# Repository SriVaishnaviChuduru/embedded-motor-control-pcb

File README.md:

# Embedded Motor Control PCB

## 📌 Project Overview
This project presents a custom-designed PCB integrating an Arduino Uno and dual L298N motor drivers into a single compact board. The objective was to reduce system size, improve wiring efficiency, and enhance reliability.

## 🚀 Key Features
- Unified PCB integrating Arduino Uno + Dual L298N drivers
- 60% reduction in overall system footprint
- Optimized routing for power and motor driver traces
- Compact and modular embedded system design

## 🛠 Tools Used
- KiCad (Schematic & PCB Layout)
- Fusion 360
- Embedded hardware testing

## 📷 Project Preview

### 🔹 Schematic

### 🔹 PCB Layout

### 🔹 3D View

## 📂 Repository Contents
- KiCad schematic files
- PCB layout files
- Project PDFs
- 3D render images

## 🎯 Learning Outcomes
- PCB schematic capture
- Layout optimization
- Power routing techniques
- Hardware debugging and board bring-up

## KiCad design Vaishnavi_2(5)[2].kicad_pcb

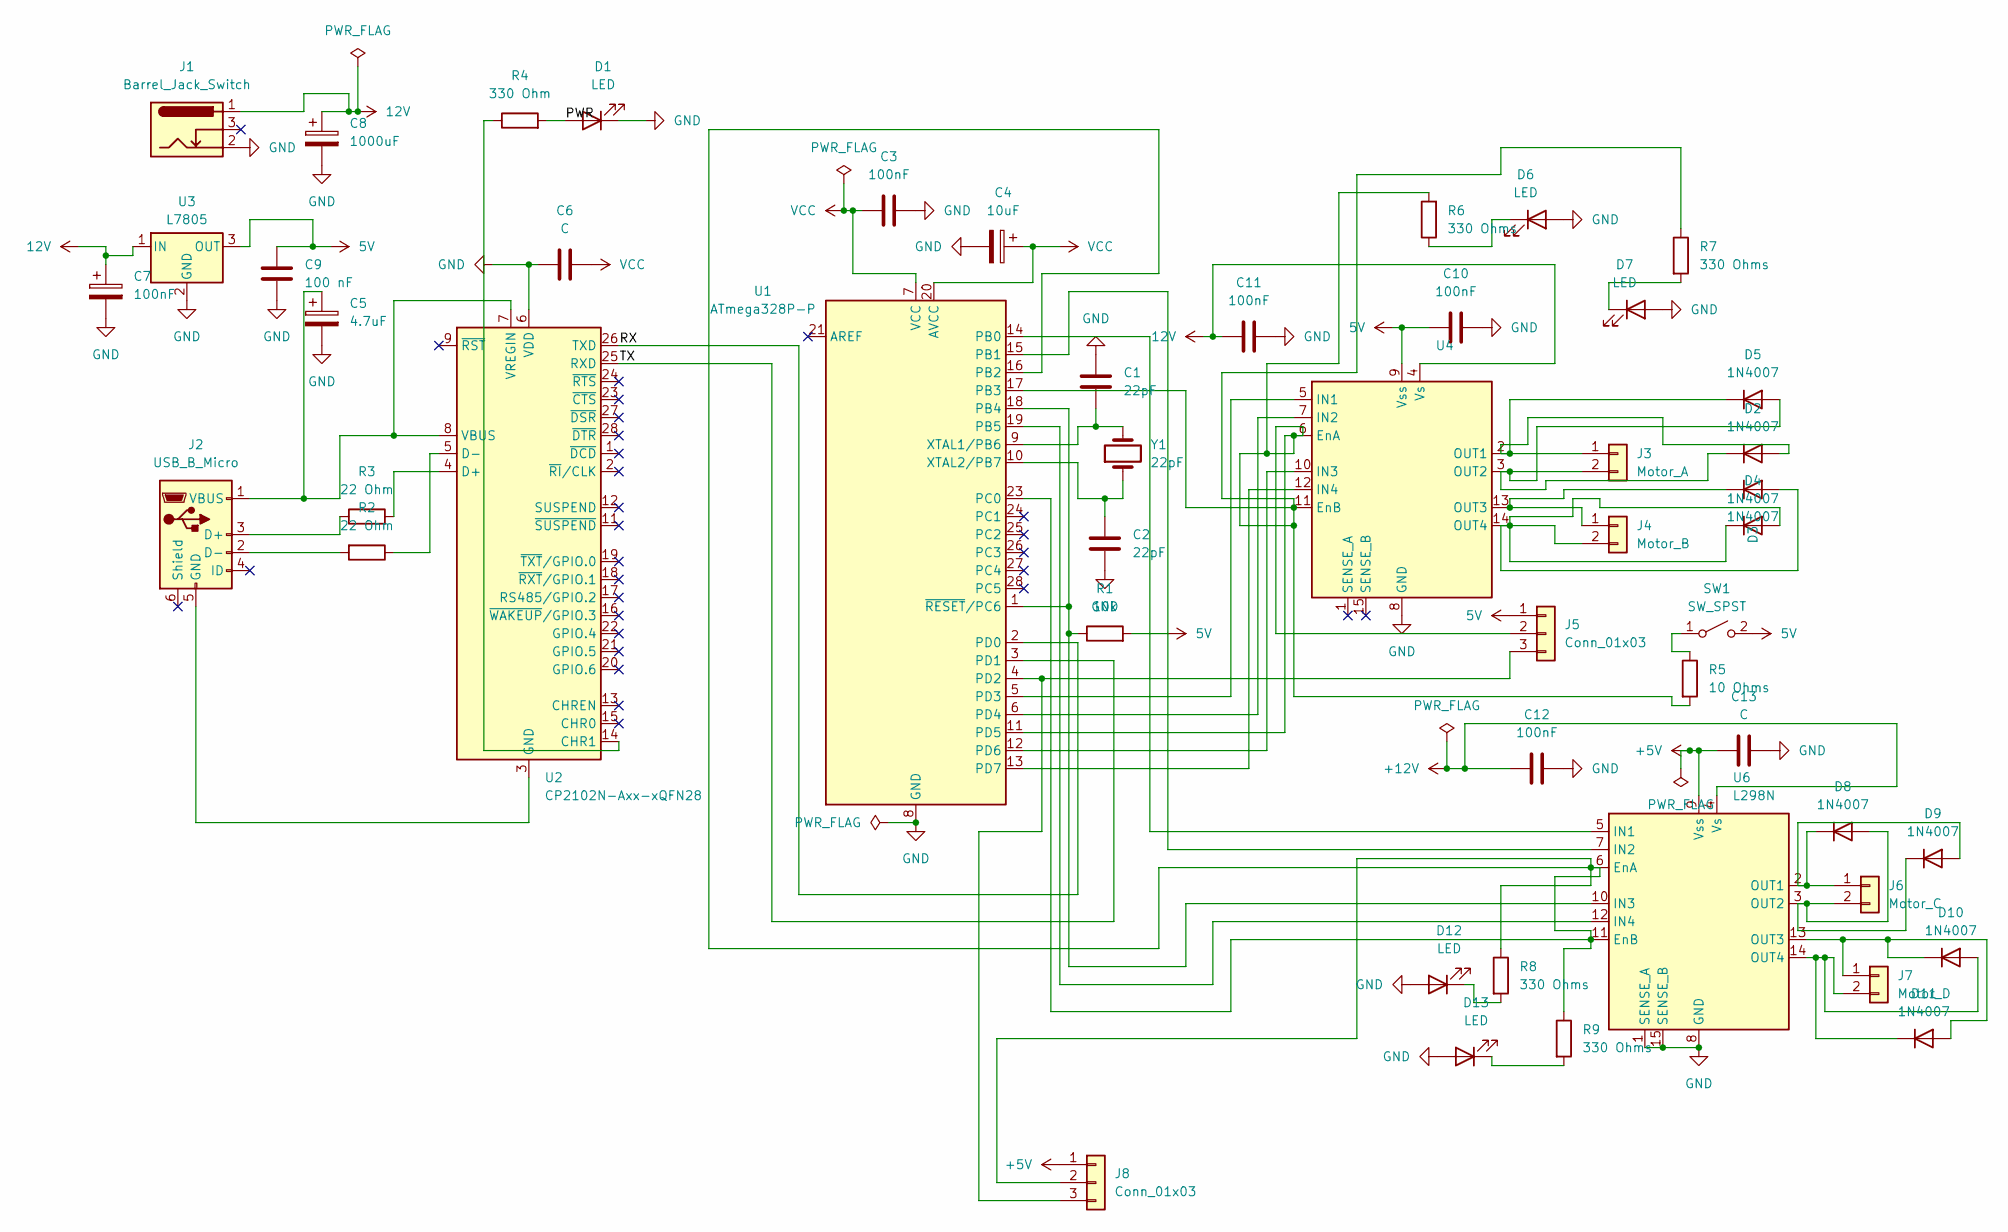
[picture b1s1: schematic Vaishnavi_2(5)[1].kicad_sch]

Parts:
C1, C2: 22pF; C_0805_2012Metric
C3, C7, C10, C11, C12: 100nF; C_0805_2012Metric
C4: 10uF; C_1210_3225Metric
C5: 4.7uF; C_1206_3216Metric
C6, C13: C; C_0805_2012Metric
C8: 1000uF; C_0805_2012Metric
C9: 100 nF; C_0805_2012Metric
D1: LED; TerminalBlock_Xinya_XY308-2.54-2P_1x02_P2.54mm_Horizontal
D2, D3, D4, D5, D8, D9, D10, D11: 1N4007; D_DO-41_SOD81_P10.16mm_Horizontal
D6, D7: LED; LED_BL-FL7680RGB
D12, D13: LED; LED_0805_2012Metric
J1: Barrel_Jack_Switch; BarrelJack_CLIFF_FC681465S_SMT_Horizontal
J2: USB_B_Micro; USB_B_OST_USB-B1HSxx_Horizontal
J3: Motor_A; TerminalBlock_Xinya_XY308-2.54-2P_1x02_P2.54mm_Horizontal
J4: Motor_B; TerminalBlock_Xinya_XY308-2.54-2P_1x02_P2.54mm_Horizontal
J5, J8: Conn_01x03; PinHeader_1x03_P1.00mm_Horizontal
J6: Motor_C; TerminalBlock_Xinya_XY308-2.54-2P_1x02_P2.54mm_Horizontal
J7: Motor_D; TerminalBlock_Xinya_XY308-2.54-2P_1x02_P2.54mm_Horizontal
R1: 10k; R_0805_2012Metric
R2, R3: 22 Ohm; R_0805_2012Metric
R4: 330 Ohm; R_0805_2012Metric
R5: 10 Ohms; R_0805_2012Metric
R6, R7, R8, R9: 330 Ohms; R_0805_2012Metric
SW1: SW_SPST; SW_SPST_Omron_B3F-40xx
U1: ATmega328P-P; DIP-28_W7.62mm
U2: CP2102N-Axx-xQFN28; QFN-28-1EP_5x5mm_P0.5mm_EP3.35x3.35mm
U3: L7805; TO-220-15_P2.54x5.08mm_StaggerOdd_Lead4.58mm_Vertical
U4: L298N; PowerSSO-16-1EP_3.9x4.9mm_P0.5mm_EP2.5x3.61mm
U6: L298N; TO-220-15_P2.54x5.08mm_StaggerOdd_Lead4.58mm_Vertical
Y1: 22pF; Crystal_SMD_3215-2Pin_3.2x1.5mm

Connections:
12V: C7.1, C8.1, C11.1, J1.1, U3.1 (IN), U4.4 (Vs)
+5V: C13.1, J8.1, U6.9 (Vss)
+12V: C12.1, U6.4 (Vs)
/PWR: D1.2 (A), R4.2
/RX: U1.2 (PD0), U2.26 (TXD)
/TX: U1.3 (PD1), U2.25 (RXD)
GND: C1.1, C2.2, C3.2, C4.2, C5.2, C6.1, C7.2, C8.2, C9.2, C10.2, C11.2, C12.2, C13.2, D1.1 (K), D6.2 (A), D7.2 (A), D12.2 (A), D13.2 (A), J1.2, U1.8 (GND), U1.22 (GND), U2.6 (VDD), U3.2 (GND), U4.8 (GND), U6.1 (SENSE_A), U6.8 (GND), U6.15 (SENSE_B)
unnamed: D2.2 (A), D5.1 (K), J3.1, U4.2 (OUT1)
unnamed: D2.1 (K), D5.2 (A), J3.2, U4.3 (OUT2)
unnamed: D3.2 (A), D4.1 (K), D4.2 (A), J4.2, U4.14 (OUT4)
unnamed: D3.1 (K), J4.1, U4.13 (OUT3)
unnamed: D6.1 (K), R6.1
unnamed: D7.1 (K), R7.2
unnamed: D8.2 (A), D9.1 (K), J6.2, U6.3 (OUT2)
unnamed: D8.1 (K), D9.2 (A), J6.1, U6.2 (OUT1)
unnamed: D10.2 (A), D11.1 (K), J7.2, U6.14 (OUT4)
unnamed: D10.1 (K), D11.2 (A), J7.1, U6.13 (OUT3)
unnamed: D12.1 (K), R8.2
unnamed: D13.1 (K), R9.2
unnamed: J2.3 (D+), R3.1
unnamed: J2.2 (D-), R2.2
unnamed: J2.5 (GND), U2.3 (GND), U2.29 (GND)
unnamed: C5.1, J2.1 (VBUS), U2.7 (VREGIN), U2.8 (VBUS)
unnamed: J5.2, R5.2, R6.2, R7.1, U1.11 (PD5), U1.17 (PB3), U4.6 (EnA), U4.11 (EnB)
unnamed: J5.3, J8.3, U1.4 (PD2)
unnamed: J8.2, R8.1, R9.1, U1.16 (PB2), U1.23 (PC0), U6.6 (EnA), U6.11 (EnB)
unnamed: R5.1, SW1.1 (A)
unnamed: U1.14 (PB0), U6.5 (IN1)
unnamed: R1.1, U1.1 (~RESET/PC6), U1.18 (PB4), U6.10 (IN3)
unnamed: U1.19 (PB5), U6.12 (IN4)
unnamed: U1.5 (PD3), U4.5 (IN1)
unnamed: U1.6 (PD4), U4.7 (IN2)
unnamed: U1.12 (PD6), U4.10 (IN3)
unnamed: U1.13 (PD7), U4.12 (IN4)
unnamed: C1.2, U1.9 (XTAL1/PB6), Y1.2
unnamed: C2.1, U1.10 (XTAL2/PB7), Y1.1
unnamed: R4.1, U2.14 (CHR1)
unnamed: R3.2, U2.4 (D+)
unnamed: R2.1, U2.5 (D-)
VCC: C3.1, C4.1, C6.2, U1.7 (VCC), U1.20 (AVCC)

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
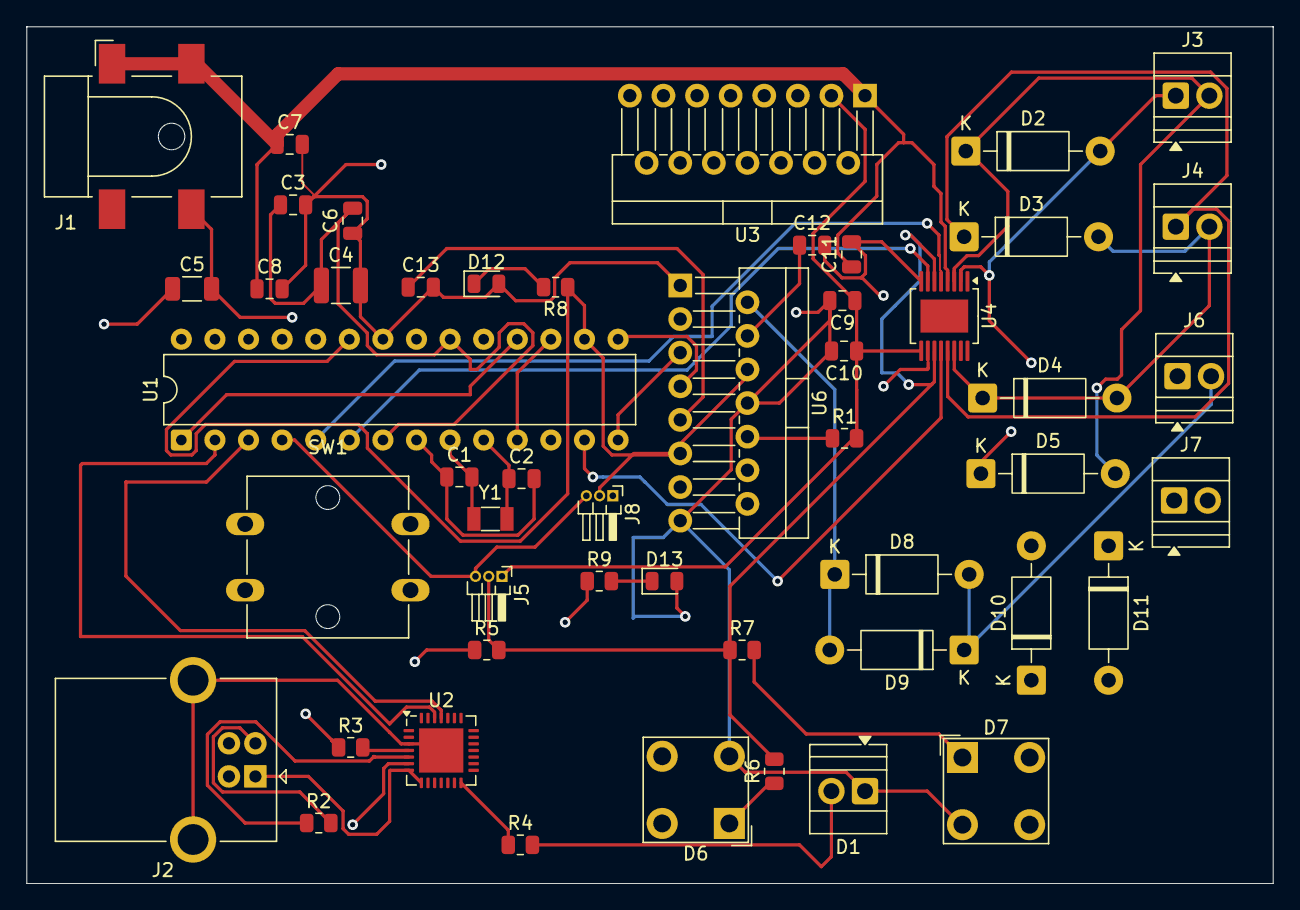
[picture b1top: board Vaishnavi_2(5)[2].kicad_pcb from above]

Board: 4 copper layers, 94.2 x 64.8 mm, 50 parts (0 on the bottom side), 42 nets.

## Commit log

2026-02-11 Add files via upload
    Initial commit – Added schematic, PCB layout, and project files
2026-02-11 Rename image.png to 3d_view.png
2026-02-11 Updated README with structured documentation and project images
